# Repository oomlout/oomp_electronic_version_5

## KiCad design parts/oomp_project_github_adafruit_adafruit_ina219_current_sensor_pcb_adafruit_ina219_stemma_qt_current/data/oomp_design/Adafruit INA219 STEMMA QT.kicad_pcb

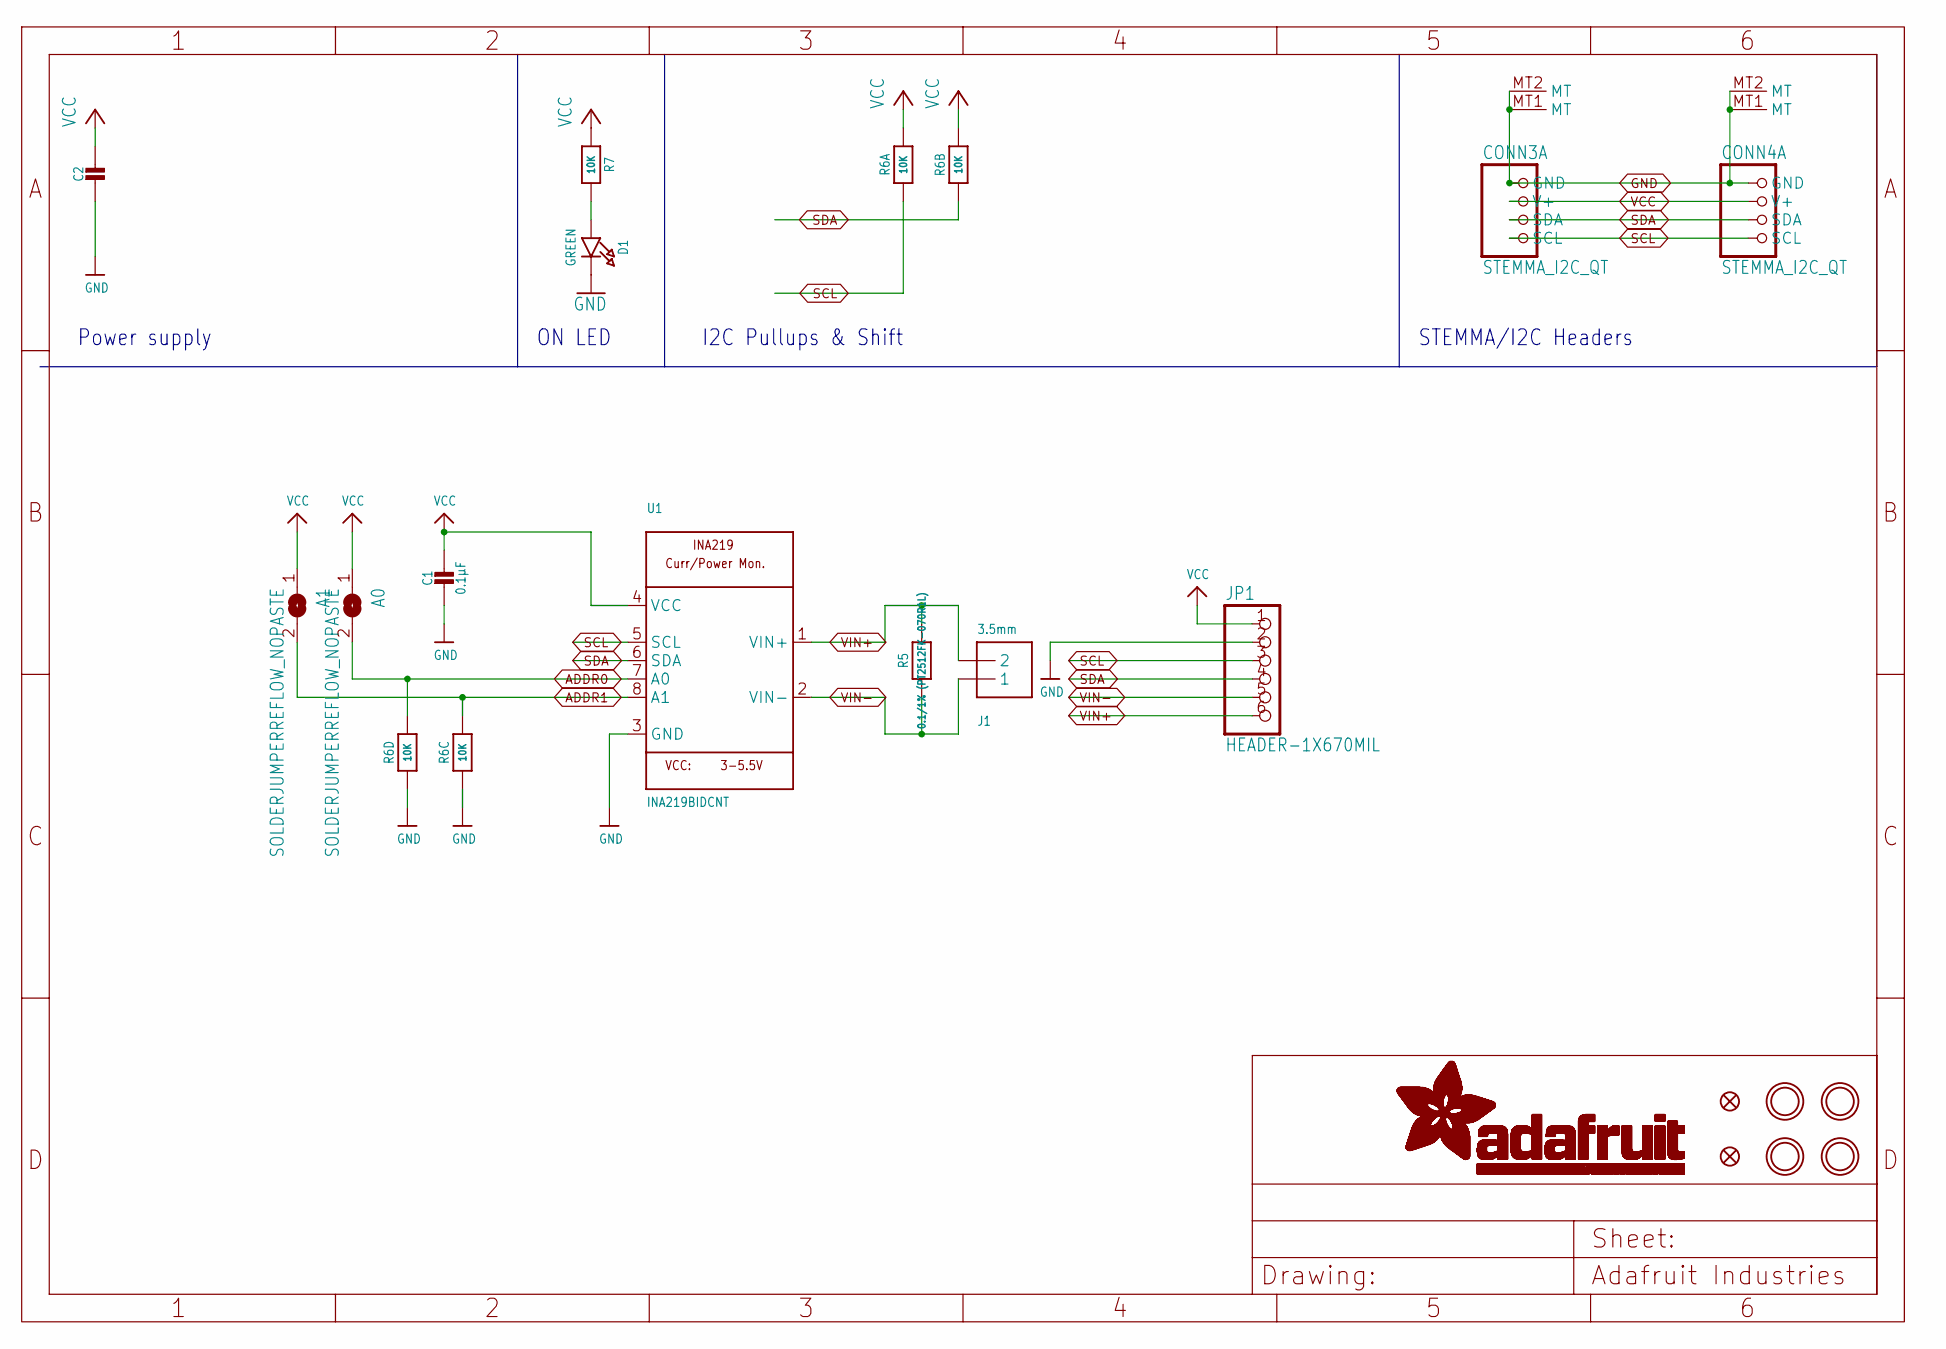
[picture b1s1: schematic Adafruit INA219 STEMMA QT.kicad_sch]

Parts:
A0, A1: SOLDERJUMPERREFLOW_NOPASTE; SOLDERJUMPER_REFLOW_NOPASTE
C1: 0.1µF; 0603-NO
C2: 10uF; 0805-NO
CONN3, CONN4: STEMMA_I2C_QT; JST_SH4
D1: GREEN; CHIPLED_0603_NOOUTLINE
FID3, FID4: FIDUCIAL_1MM
J1: 3.5mm; TERMBLOCK_1X2-3.5MM
JP1: HEADER-1X670MIL; 1X06_ROUND_70
R5: 0.1/1% (PT2512FK-070R1L); 2512
R6: 10K; RESPACK_4X0603
R7: 10K; 0603-NO
U1: INA219BIDCNT; SOT23-8
U$20, U$21, U$25, U$27: MOUNTINGHOLE2.5; MOUNTINGHOLE_2.5_PLATED

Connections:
ADDR0: A0.2, R6.5 (2), U1.7 (A0)
ADDR1: A1.2, R6.6 (2), U1.8 (A1)
GND: C1.2, C2.2, CONN3.1 (GND), CONN3.MT1 (MT), CONN3.MT2 (MT), CONN4.1 (GND), CONN4.MT1 (MT), CONN4.MT2 (MT), D1.C, JP1.2, R6.3 (1), R6.4 (1), U1.3 (GND)
unnamed: D1.A, R7.2
SCL: CONN3.4 (SCL), CONN4.4 (SCL), JP1.3, R6.1, U1.5 (SCL)
SDA: CONN3.3 (SDA), CONN4.3 (SDA), JP1.4, R6.2 (1), U1.6 (SDA)
VCC: A0.1, A1.1, C1.1, C2.1, CONN3.2 (V+), CONN4.2 (V+), JP1.1, R6.7 (2), R6.8 (2), R7.1, U1.4 (VCC)
VIN+: J1.2, JP1.6, R5.2, U1.1 (VIN+)
VIN-: J1.1, JP1.5, R5.1, U1.2 (VIN-)

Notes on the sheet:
ON LED
I2C Pullups & Shift
Power supply
STEMMA/I2C Headers

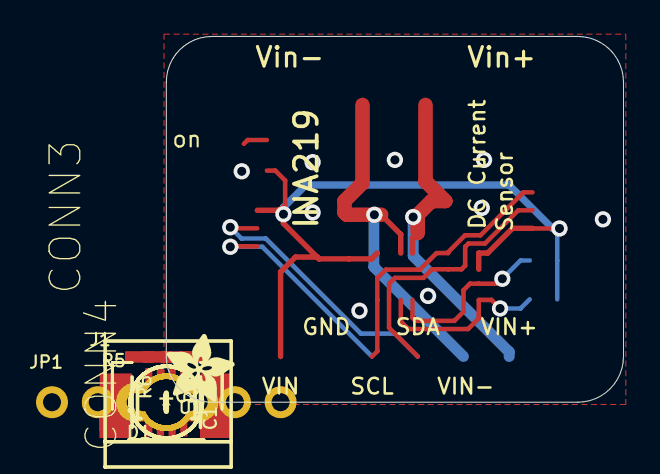
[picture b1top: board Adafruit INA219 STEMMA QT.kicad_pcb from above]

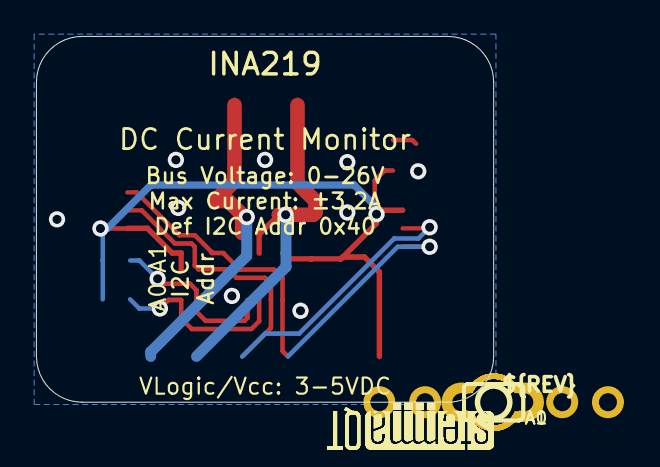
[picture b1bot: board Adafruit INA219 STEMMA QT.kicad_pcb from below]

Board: 2 copper layers, 25.4 x 20.3 mm, 23 parts (5 on the bottom side), 9 nets.

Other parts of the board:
U$29: ADAFRUIT_3.5MM
U$30: PCBFEAT-REV-040
U$31, U$32: STEMMAQT

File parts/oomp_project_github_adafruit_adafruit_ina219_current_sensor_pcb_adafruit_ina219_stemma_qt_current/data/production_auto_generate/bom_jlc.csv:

Comment,Designator,Footprint,LCSC Part #
,JP1,Adafruit INA219 STEMMA QT-import-fps:1X06_ROUND_70,C37208
,U$29,Adafruit INA219 STEMMA QT-import-fps:ADAFRUIT_3.5MM,
,U$30,Adafruit INA219 STEMMA QT-import-fps:PCBFEAT-REV-040,
,"A0,A1",Adafruit INA219 STEMMA QT-import-fps:SOLDERJUMPER_REFLOW_NOPASTE,
,"U$31,U$32",Adafruit INA219 STEMMA QT-import-fps:STEMMAQT,
0.1/1% (PT2512FK-070R1L),R5,Adafruit INA219 STEMMA QT-import-fps:2512,
0.1µF,C1,Adafruit INA219 STEMMA QT-import-fps:0603-NO,C14663
10K,R7,Adafruit INA219 STEMMA QT-import-fps:0603-NO,C98220
10K,R6,Adafruit INA219 STEMMA QT-import-fps:RESPACK_4X0603,C98220
10uF,C2,Adafruit INA219 STEMMA QT-import-fps:0805-NO,
3.5mm,J1,Adafruit INA219 STEMMA QT-import-fps:TERMBLOCK_1X2-3.5MM,
GREEN,D1,Adafruit INA219 STEMMA QT-import-fps:CHIPLED_0603_NOOUTLINE,
INA219BIDCNT,U1,Adafruit INA219 STEMMA QT-import-fps:SOT23-8,
STEMMA_I2C_QT,"CONN3,CONN4",Adafruit INA219 STEMMA QT-import-fps:JST_SH4,C160404

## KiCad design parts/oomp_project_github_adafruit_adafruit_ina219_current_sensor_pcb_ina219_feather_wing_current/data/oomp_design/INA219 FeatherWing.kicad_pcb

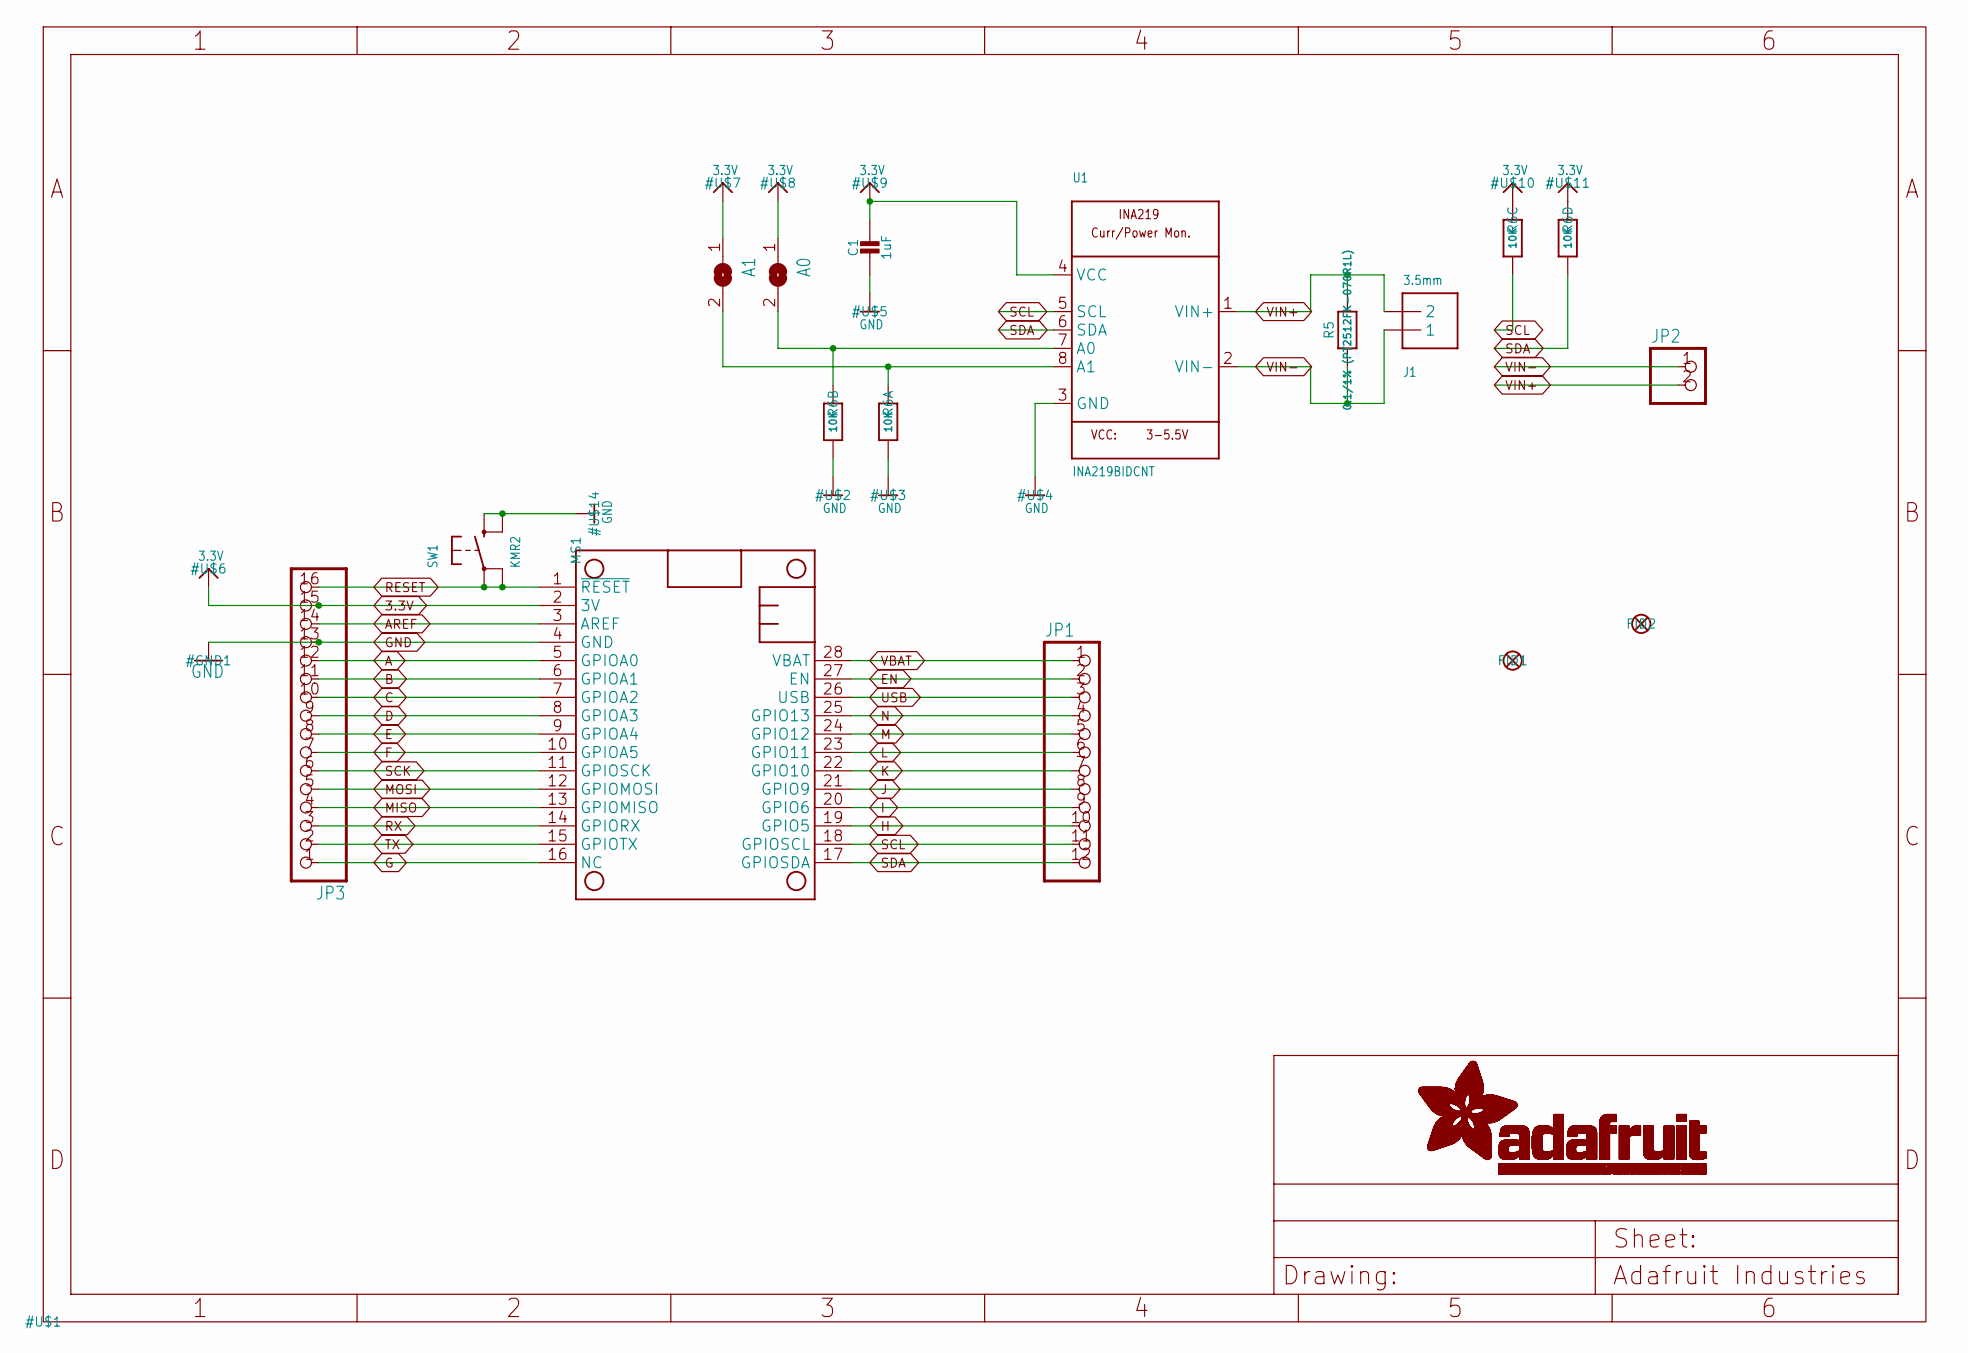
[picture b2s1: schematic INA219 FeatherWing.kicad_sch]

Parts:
A0, A1: SOLDERJUMPERREFLOW_NOPASTE; SOLDERJUMPER_REFLOW_NOPASTE
C1: 1uF; 0805-NO@1
FID1, FID2: FIDUCIAL_1MM
J1: 3.5mm; TERMBLOCK_1X2-3.5MM
JP1: HEADER-1X1276MIL; 1X12_ROUND_76MIL
JP2: HEADER-1X2ROUND; 1X02_ROUND
JP3: HEADER-1X16_76MIL; 1X16_ROUND_76MIL
MS1: FEATHERWING
R5: 0.1/1% (PT2512FK-070R1L); 2512
R6: 10K; RESPACK_4X0603
SW1: KMR2; BTN_KMR2_4.6X2.8
U1: INA219BIDCNT; SOT23-8

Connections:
3.3V: A0.1, A1.1, C1.1, JP3.15, MS1.2 (3V), R6.5 (2), R6.6 (2), U1.4 (VCC)
A: JP3.12, MS1.5 (GPIOA0)
AREF: JP3.14, MS1.3 (AREF)
B: JP3.11, MS1.6 (GPIOA1)
C: JP3.10, MS1.7 (GPIOA2)
D: JP3.9, MS1.8 (GPIOA3)
E: JP3.8, MS1.9 (GPIOA4)
EN: JP1.2, MS1.27 (EN)
F: JP3.7, MS1.10 (GPIOA5)
G: JP3.1, MS1.16 (NC)
GND: C1.2, JP3.13, MS1.4 (GND), R6.7 (2), R6.8 (2), SW1.B (S), SW1.B' (S1), U1.3 (GND)
H: JP1.10, MS1.19 (GPIO5)
I: JP1.9, MS1.20 (GPIO6)
J: JP1.8, MS1.21 (GPIO9)
K: JP1.7, MS1.22 (GPIO10)
L: JP1.6, MS1.23 (GPIO11)
M: JP1.5, MS1.24 (GPIO12)
MISO: JP3.4, MS1.13 (GPIOMISO)
MOSI: JP3.5, MS1.12 (GPIOMOSI)
N: JP1.4, MS1.25 (GPIO13)
unnamed: A1.2, R6.1, U1.8 (A1)
unnamed: A0.2, R6.2 (1), U1.7 (A0)
RESET: JP3.16, MS1.1 (~RESET), SW1.A, SW1.A' (P1)
RX: JP3.3, MS1.14 (GPIORX)
SCK: JP3.6, MS1.11 (GPIOSCK)
SCL: JP1.11, MS1.18 (GPIOSCL), R6.3 (1), U1.5 (SCL)
SDA: JP1.12, MS1.17 (GPIOSDA), R6.4 (1), U1.6 (SDA)
TX: JP3.2, MS1.15 (GPIOTX)
USB: JP1.3, MS1.26 (USB)
VBAT: JP1.1, MS1.28 (VBAT)
VIN+: J1.2, JP2.2, R5.2, U1.1 (VIN+)
VIN-: J1.1, JP2.1, R5.1, U1.2 (VIN-)

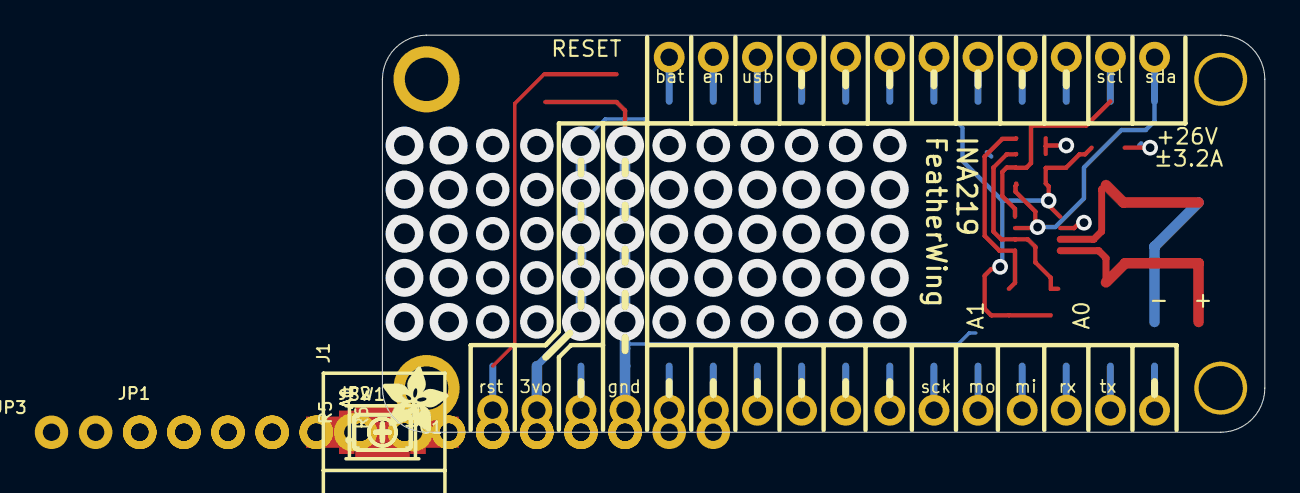
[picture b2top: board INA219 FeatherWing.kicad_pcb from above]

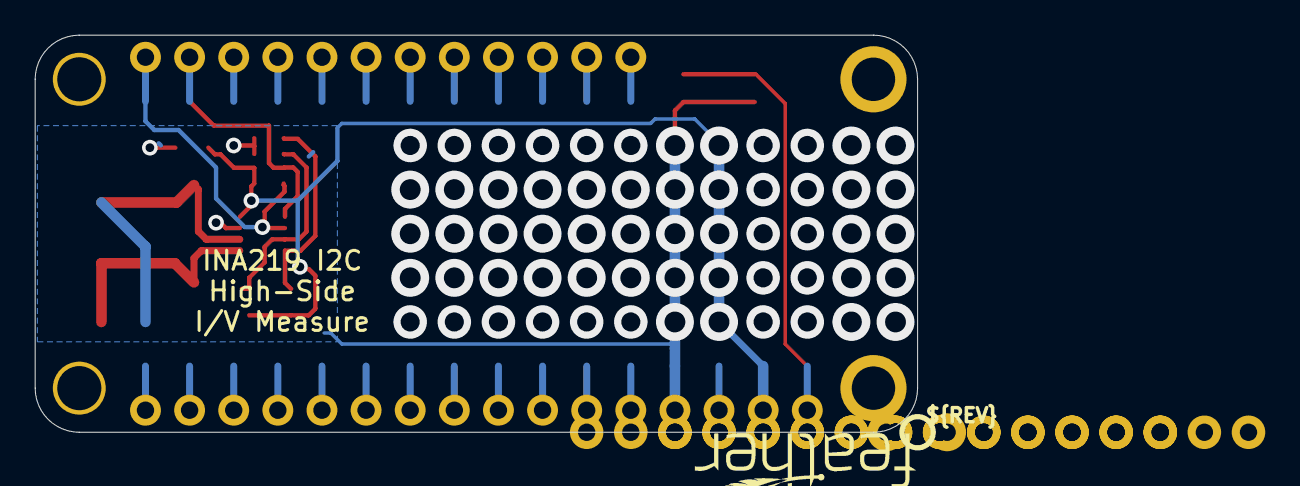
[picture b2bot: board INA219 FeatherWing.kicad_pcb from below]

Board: 2 copper layers, 50.8 x 22.9 mm, 19 parts (2 on the bottom side), 32 nets.

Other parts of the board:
U$12: SYMBOL_PLUS
U$13: SYMBOL_MINUS
U$15: FEATHERLOGO_SMALL
U$16: ADAFRUIT_3.5MM
U$17: PCBFEAT-REV-040

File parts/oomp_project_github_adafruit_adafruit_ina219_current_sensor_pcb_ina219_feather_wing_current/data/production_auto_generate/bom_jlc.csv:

Comment,Designator,Footprint,LCSC Part #
,JP2,INA219 FeatherWing-import-fps:1X02_ROUND,C492401
,JP1,INA219 FeatherWing-import-fps:1X12_ROUND_76MIL,C7501588
,JP3,INA219 FeatherWing-import-fps:1X16_ROUND_76MIL,C7501270
,U$16,INA219 FeatherWing-import-fps:ADAFRUIT_3.5MM,
,U$15,INA219 FeatherWing-import-fps:FEATHERLOGO_SMALL,
,U$17,INA219 FeatherWing-import-fps:PCBFEAT-REV-040,
,"A0,A1",INA219 FeatherWing-import-fps:SOLDERJUMPER_REFLOW_NOPASTE,
,U$13,INA219 FeatherWing-import-fps:SYMBOL_MINUS,
,U$12,INA219 FeatherWing-import-fps:SYMBOL_PLUS,
0.1/1% (PT2512FK-070R1L),R5,INA219 FeatherWing-import-fps:2512,
10K,R6,INA219 FeatherWing-import-fps:RESPACK_4X0603,C98220
1uF,C1,INA219 FeatherWing-import-fps:0805-NO@1,
3.5mm,J1,INA219 FeatherWing-import-fps:TERMBLOCK_1X2-3.5MM,
FEATHERWING,MS1,INA219 FeatherWing-import-fps:FEATHERWING,
INA219BIDCNT,U1,INA219 FeatherWing-import-fps:SOT23-8,
KMR2,SW1,INA219 FeatherWing-import-fps:BTN_KMR2_4.6X2.8,

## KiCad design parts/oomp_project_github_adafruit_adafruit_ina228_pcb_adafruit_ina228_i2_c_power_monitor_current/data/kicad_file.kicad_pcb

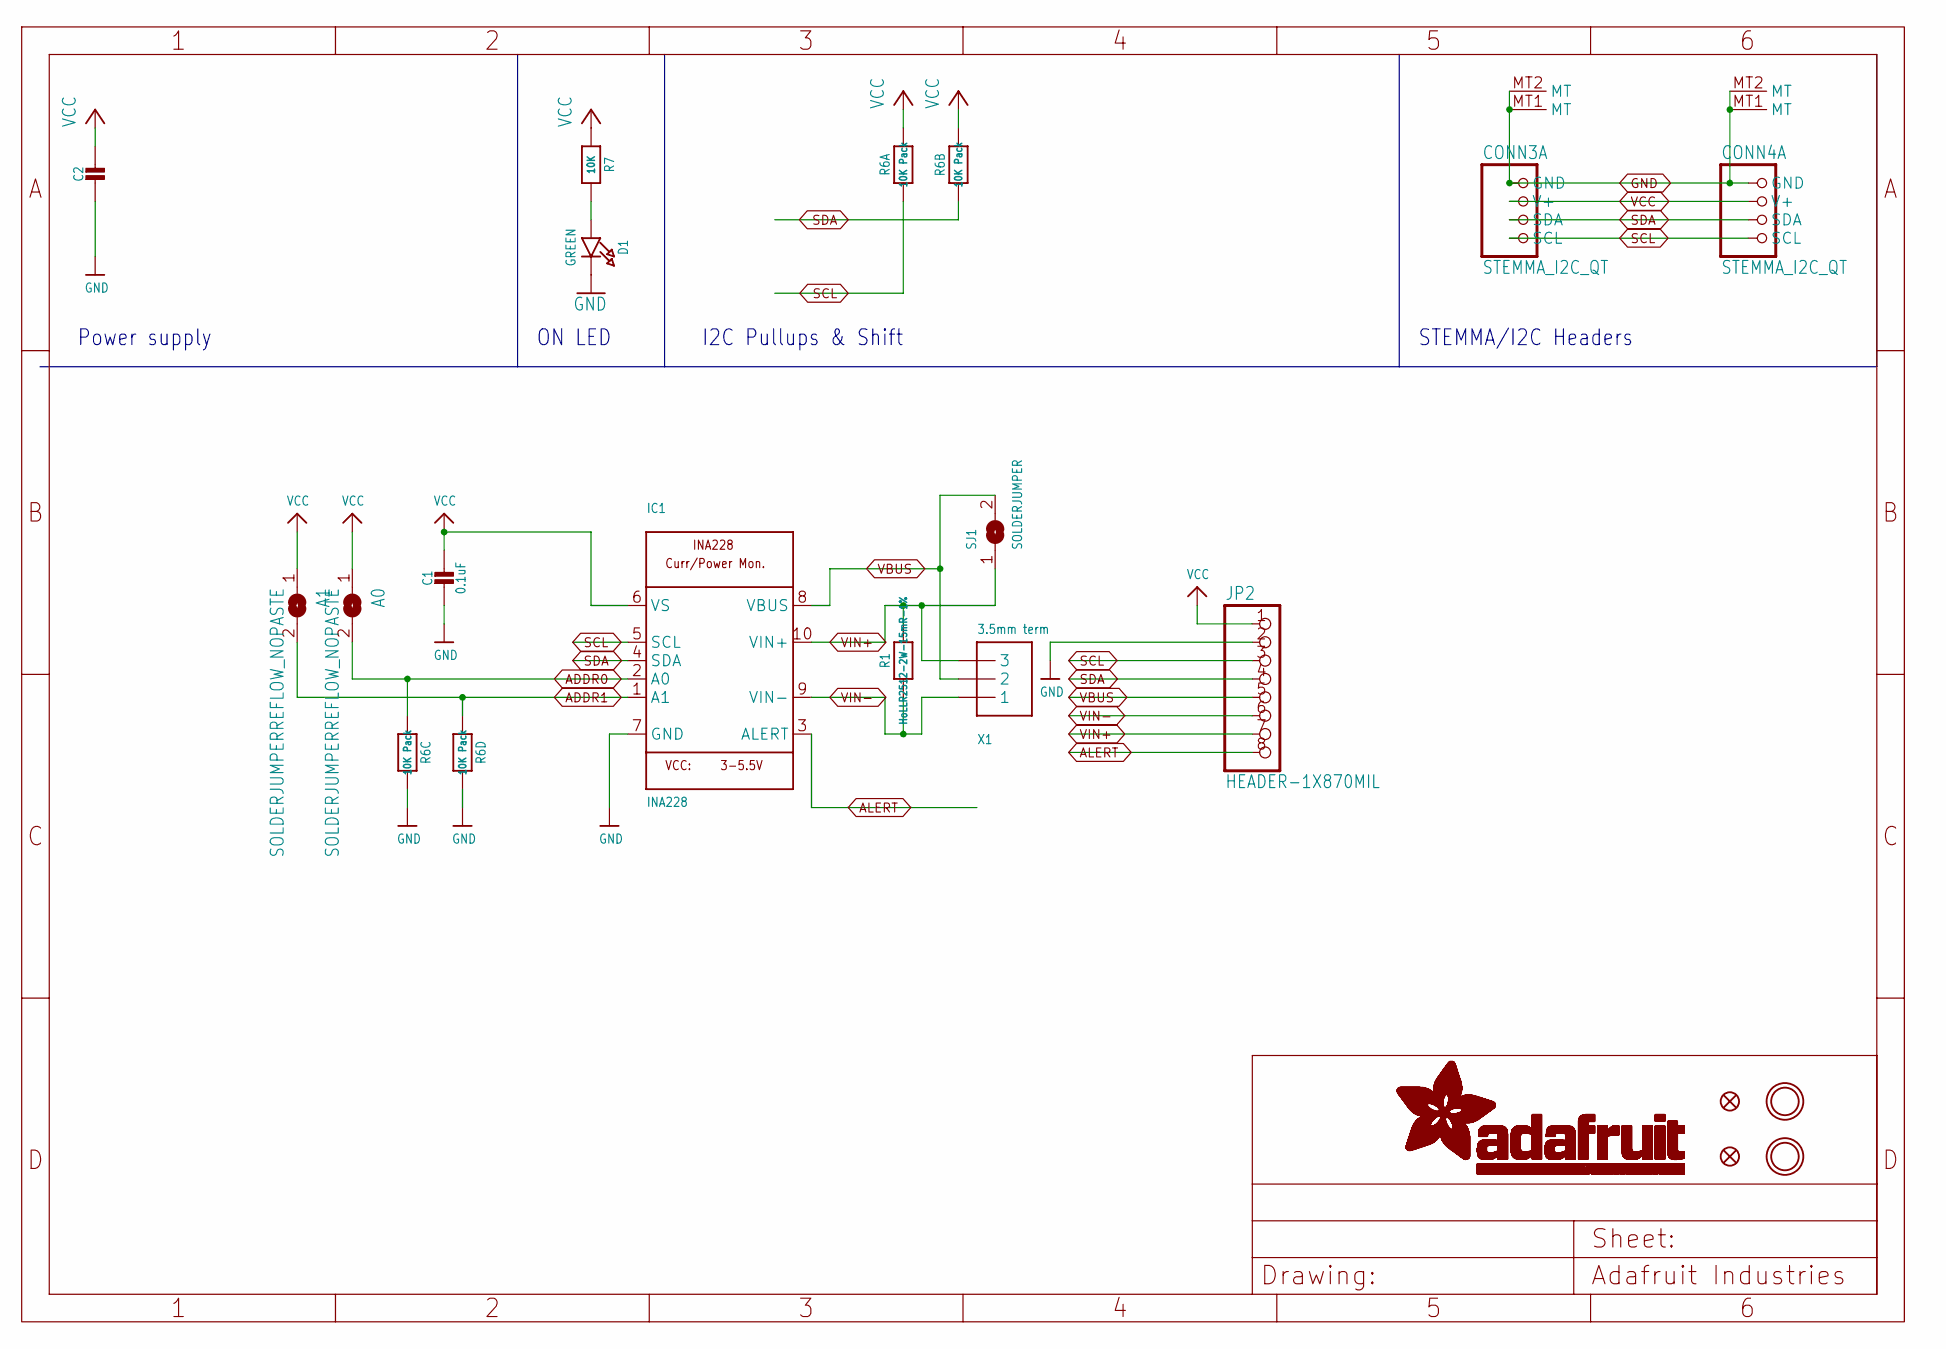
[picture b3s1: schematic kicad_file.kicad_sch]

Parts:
A0, A1: SOLDERJUMPERREFLOW_NOPASTE; SOLDERJUMPER_REFLOW_NOPASTE
C1: 0.1uF; 0603-NO
C2: 10uF; 0805-NO
CONN3, CONN4: STEMMA_I2C_QT; JST_SH4; LCSC C2845363
D1: GREEN; CHIPLED_0603_NOOUTLINE
FID3, FID4: FIDUCIAL_1MM
IC1: INA228; MSOP10
JP2: HEADER-1X870MIL; 1X08_ROUND_70
R1: HoLLR2512-2W-15mR-1%; 2512
R6: 10K Pack; RESPACK_4X0603
R7: 10K; 0603-NO
SJ1: SOLDERJUMPER; SOLDERJUMPER_ARROW_NOPASTE
U$20, U$21: MOUNTINGHOLE2.5; MOUNTINGHOLE_2.5_PLATED
X1: 3.5mm term; TERMBLOCK_1X3-3.5MM

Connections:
ADDR0: A0.2, IC1.2 (A0), R6.3 (1)
ADDR1: A1.2, IC1.1 (A1), R6.4 (1)
ALERT: IC1.3 (ALERT), JP2.8
GND: C1.2, C2.2, CONN3.1 (GND), CONN3.MT1 (MT), CONN3.MT2 (MT), CONN4.1 (GND), CONN4.MT1 (MT), CONN4.MT2 (MT), D1.C, IC1.7 (GND), JP2.2, R6.5 (2), R6.6 (2)
unnamed: D1.A, R7.2
SCL: CONN3.4 (SCL), CONN4.4 (SCL), IC1.5 (SCL), JP2.3, R6.1
SDA: CONN3.3 (SDA), CONN4.3 (SDA), IC1.4 (SDA), JP2.4, R6.2 (1)
VBUS: IC1.8 (VBUS), JP2.5, SJ1.2, X1.2
VCC: A0.1, A1.1, C1.1, C2.1, CONN3.2 (V+), CONN4.2 (V+), IC1.6 (VS), JP2.1, R6.7 (2), R6.8 (2), R7.1
VIN+: IC1.10 (VIN+), JP2.7, R1.2, SJ1.1, X1.3
VIN-: IC1.9 (VIN-), JP2.6, R1.1, X1.1

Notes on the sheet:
ON LED
Power supply
I2C Pullups & Shift
STEMMA/I2C Headers

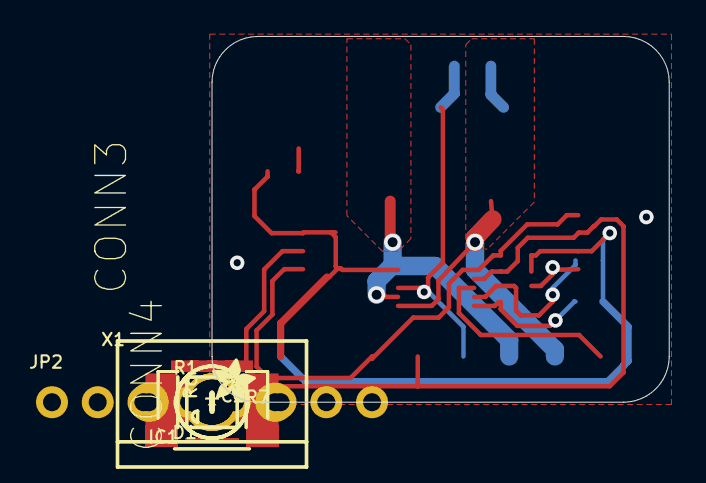
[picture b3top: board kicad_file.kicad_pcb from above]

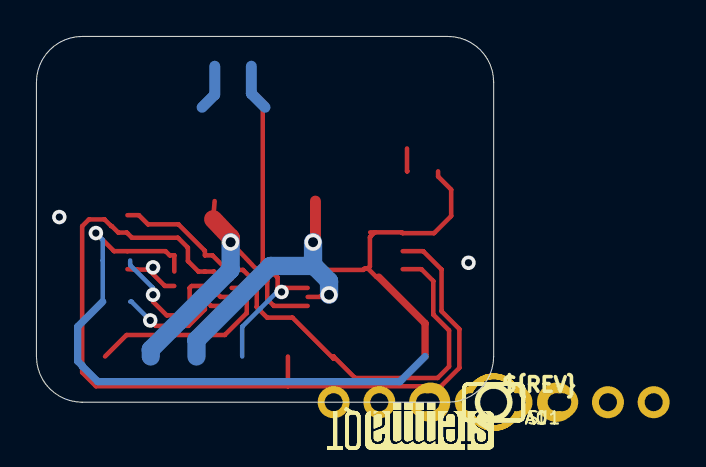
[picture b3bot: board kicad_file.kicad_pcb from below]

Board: 2 copper layers, 25.4 x 20.3 mm, 43 parts (16 on the bottom side), 11 nets.

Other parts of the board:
PLABEL0: PLABEL0
PLABEL1: PLABEL1
PLABEL2: PLABEL2
PLABEL3: PLABEL3
PLABEL4: PLABEL4
PLABEL5: PLABEL5
PLABEL6: PLABEL6
PLABEL7: PLABEL7
PLABEL8: PLABEL8
PLABEL9: PLABEL9
PLABEL10: PLABEL10
PLABEL11: PLABEL11
PLABEL12: PLABEL12
PLABEL13: PLABEL13
PLABEL14: PLABEL14
PLABEL15: PLABEL15
PLABEL16: PLABEL16
PLABEL17: PLABEL17
PLABEL18: PLABEL18
PLABEL19: PLABEL19
PLABEL20: PLABEL20
U$1: ADAFRUIT_2.5MM
U$30: PCBFEAT-REV-040
U$31, U$32: STEMMAQT

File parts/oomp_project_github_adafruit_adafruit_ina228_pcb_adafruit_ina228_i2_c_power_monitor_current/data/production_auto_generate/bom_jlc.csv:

Comment,Designator,Footprint,LCSC Part #
,JP2,Adafruit INA228 I2C Power Monitor-import-fps:1X08_ROUND_70,C492421
,U$1,Adafruit INA228 I2C Power Monitor-import-fps:ADAFRUIT_2.5MM,
,U$30,Adafruit INA228 I2C Power Monitor-import-fps:PCBFEAT-REV-040,
,PLABEL0,Adafruit INA228 I2C Power Monitor-import-fps:PLABEL0,
,PLABEL1,Adafruit INA228 I2C Power Monitor-import-fps:PLABEL1,
,PLABEL10,Adafruit INA228 I2C Power Monitor-import-fps:PLABEL10,
,PLABEL11,Adafruit INA228 I2C Power Monitor-import-fps:PLABEL11,
,PLABEL12,Adafruit INA228 I2C Power Monitor-import-fps:PLABEL12,
,PLABEL13,Adafruit INA228 I2C Power Monitor-import-fps:PLABEL13,
,PLABEL14,Adafruit INA228 I2C Power Monitor-import-fps:PLABEL14,
,PLABEL15,Adafruit INA228 I2C Power Monitor-import-fps:PLABEL15,
,PLABEL16,Adafruit INA228 I2C Power Monitor-import-fps:PLABEL16,
,PLABEL17,Adafruit INA228 I2C Power Monitor-import-fps:PLABEL17,
,PLABEL18,Adafruit INA228 I2C Power Monitor-import-fps:PLABEL18,
,PLABEL19,Adafruit INA228 I2C Power Monitor-import-fps:PLABEL19,
,PLABEL2,Adafruit INA228 I2C Power Monitor-import-fps:PLABEL2,
,PLABEL20,Adafruit INA228 I2C Power Monitor-import-fps:PLABEL20,
,PLABEL3,Adafruit INA228 I2C Power Monitor-import-fps:PLABEL3,
,PLABEL4,Adafruit INA228 I2C Power Monitor-import-fps:PLABEL4,
,PLABEL5,Adafruit INA228 I2C Power Monitor-import-fps:PLABEL5,
,PLABEL6,Adafruit INA228 I2C Power Monitor-import-fps:PLABEL6,
,PLABEL7,Adafruit INA228 I2C Power Monitor-import-fps:PLABEL7,
,PLABEL8,Adafruit INA228 I2C Power Monitor-import-fps:PLABEL8,
,PLABEL9,Adafruit INA228 I2C Power Monitor-import-fps:PLABEL9,
,"A0,A1",Adafruit INA228 I2C Power Monitor-import-fps:SOLDERJUMPER_REFLOW_NOPASTE,
,"U$31,U$32",Adafruit INA228 I2C Power Monitor-import-fps:STEMMAQT,
0.1uF,C1,Adafruit INA228 I2C Power Monitor-import-fps:0603-NO,C14663
10K,R7,Adafruit INA228 I2C Power Monitor-import-fps:0603-NO,C98220
10K Pack,R6,Adafruit INA228 I2C Power Monitor-import-fps:RESPACK_4X0603,C98220
10uF,C2,Adafruit INA228 I2C Power Monitor-import-fps:0805-NO,
3.5mm term,X1,Adafruit INA228 I2C Power Monitor-import-fps:TERMBLOCK_1X3-3.5MM,
GREEN,D1,Adafruit INA228 I2C Power Monitor-import-fps:CHIPLED_0603_NOOUTLINE,
HoLLR2512-2W-15mR-1%,R1,Adafruit INA228 I2C Power Monitor-import-fps:2512,
INA228,IC1,Adafruit INA228 I2C Power Monitor-import-fps:MSOP10,
STEMMA_I2C_QT,"CONN3,CONN4",Adafruit INA228 I2C Power Monitor-import-fps:JST_SH4,C160404

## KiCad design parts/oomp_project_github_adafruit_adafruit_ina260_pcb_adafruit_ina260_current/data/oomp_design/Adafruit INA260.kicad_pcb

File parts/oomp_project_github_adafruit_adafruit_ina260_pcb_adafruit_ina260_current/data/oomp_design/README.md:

# OOMP KiCad design copy

Open `Adafruit INA260.kicad_pro` (or the `.kicad_pcb` / `.kicad_sch`) in KiCad. Local OOMP libraries are under `libraries/`. Original inputs are preserved in [../original/](../original/).

Only verified unchanged installed KiCad defaults were renamed. Modified, custom, unmatched and unavailable items remain unchanged. Soldering variants are never swapped during conversion. Existing pad coordinates, nets and UUIDs are preserved.

See [conversion_report.yaml](conversion_report.yaml) for every conversion and skip. Copy this directory before editing; regeneration refuses to overwrite edited design files.

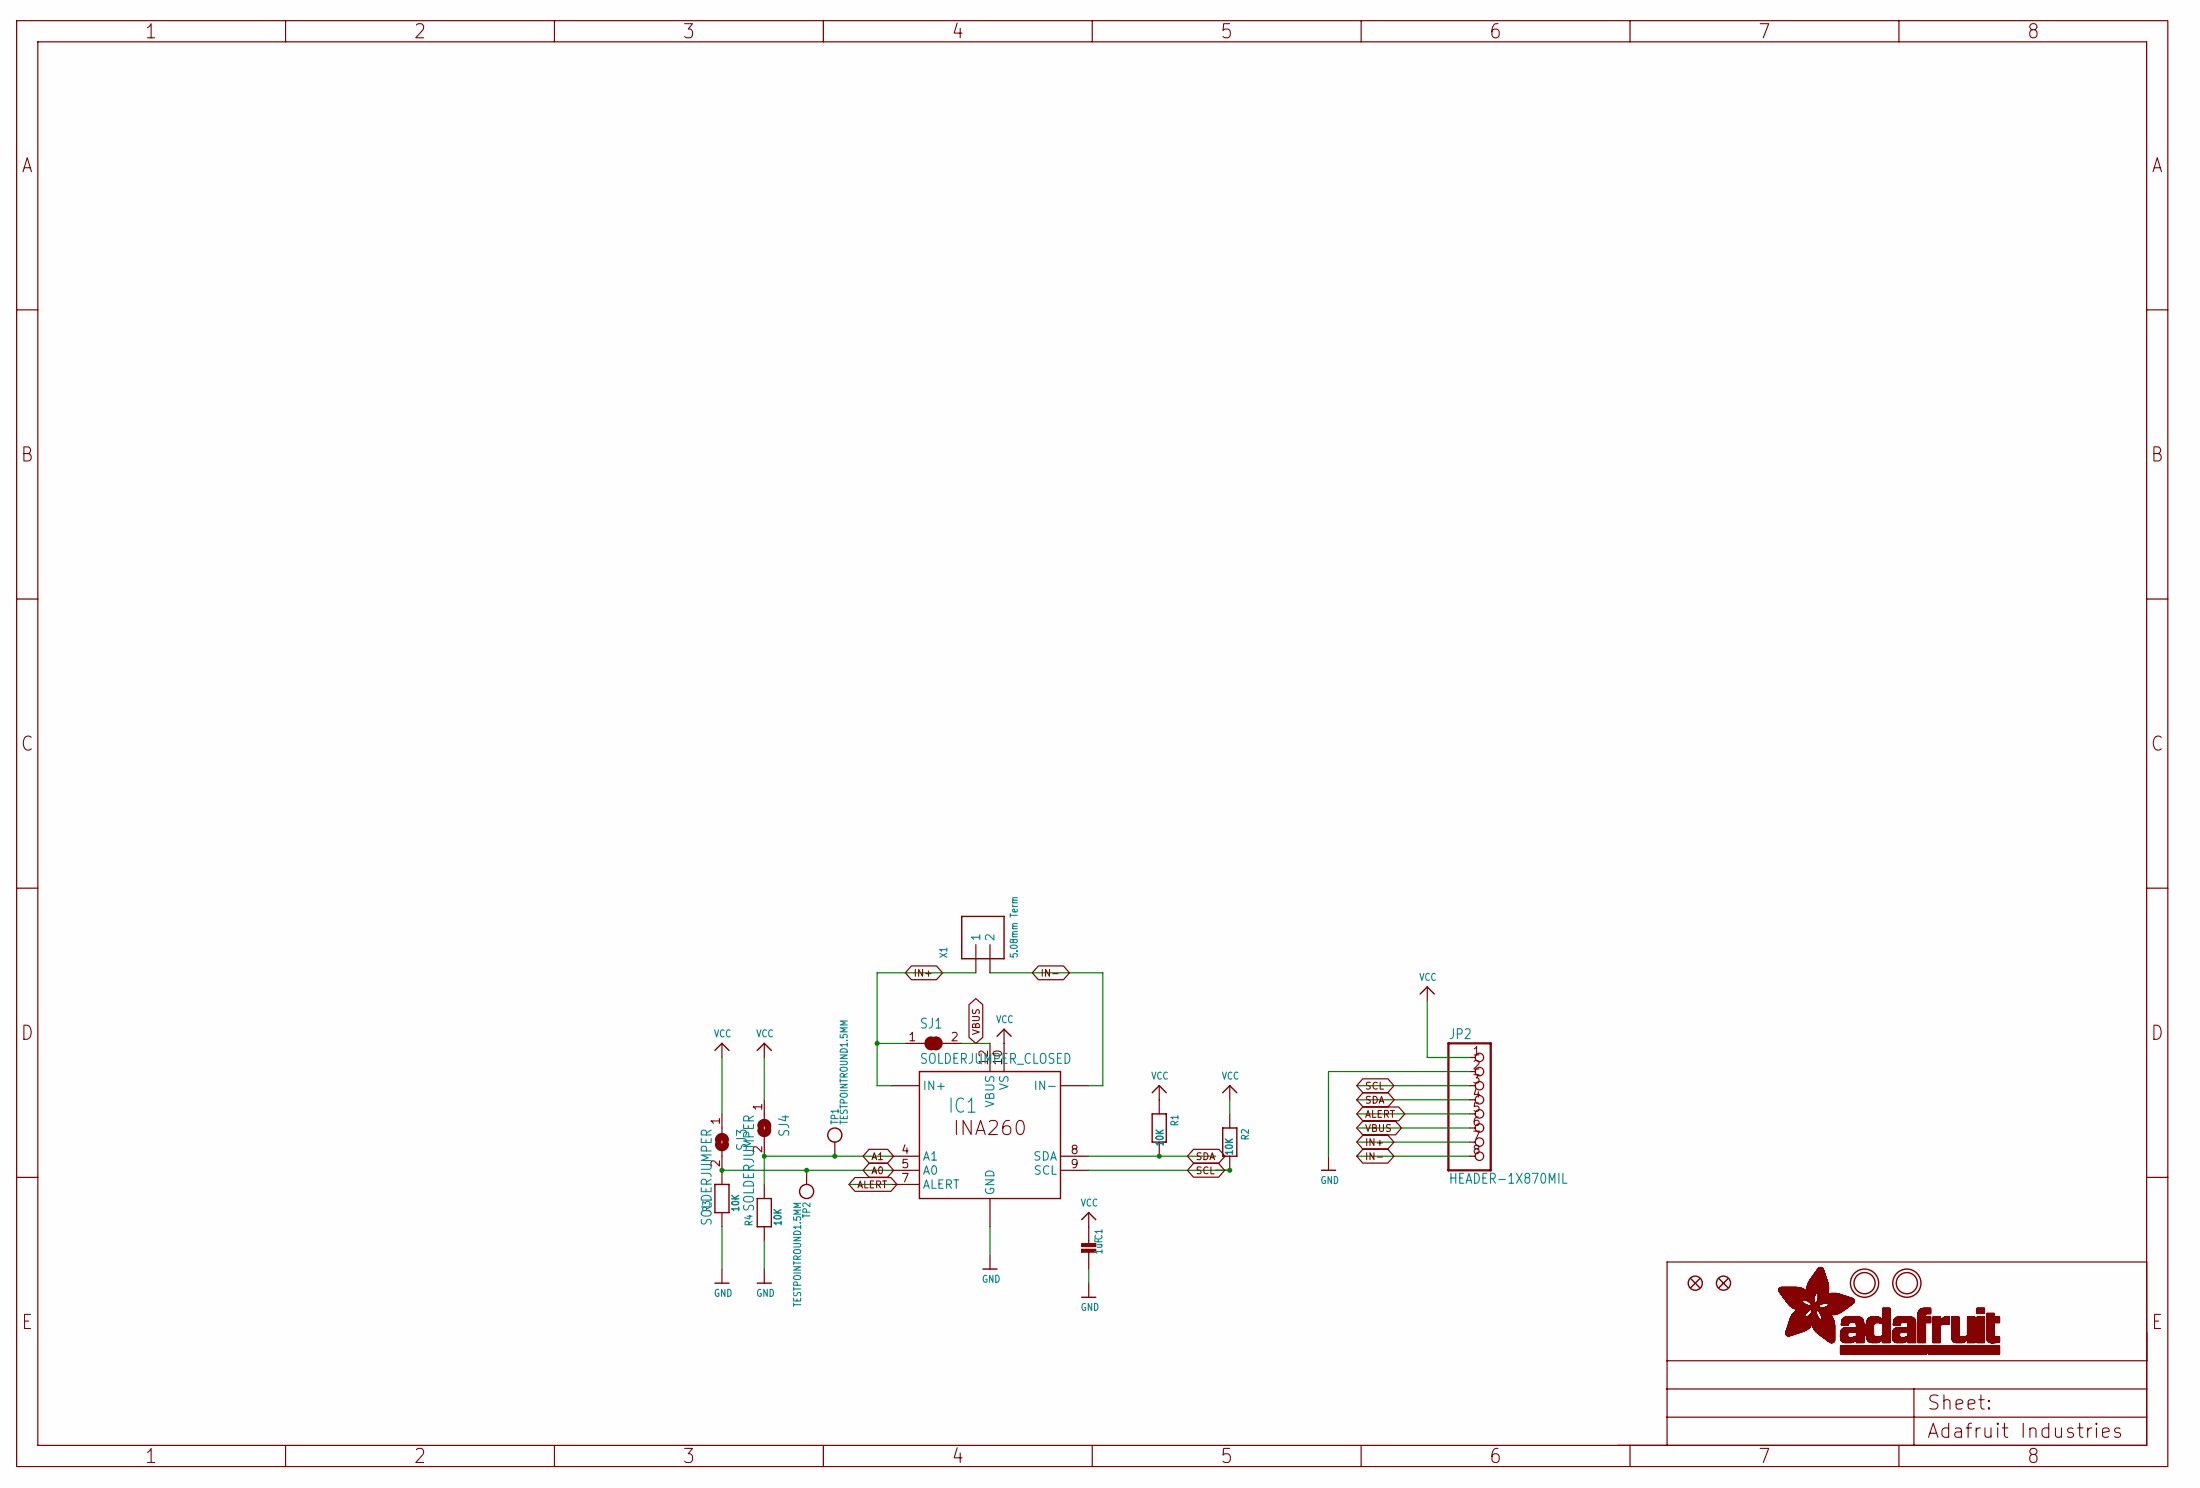
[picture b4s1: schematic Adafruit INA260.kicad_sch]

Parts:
C1: 1uF; 0603-NO
FID3, FID4: MICROBUILDER_FIDUCIAL""; MICROBUILDER_FIDUCIAL_1MM
IC1: INA260; TSSOP16
JP2: HEADER-1X870MIL; 1X08_ROUND_70
R1, R2, R3, R4: 10K; 0603-NO
SJ1: SOLDERJUMPER_CLOSED; SOLDERJUMPER_CLOSEDWIRE
SJ3, SJ4: SOLDERJUMPER; SOLDERJUMPER_ARROW_NOPASTE
TP1, TP2: TESTPOINTROUND1.5MM; TESTPOINT_ROUND_1.5MM
U$7, U$8: MOUNTINGHOLE2.5; MOUNTINGHOLE_2.5_PLATED
X1: 5.08mm Term; TERMBLOCK_508_1X2

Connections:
A0: IC1.5 (A0), R3.2, SJ3.2, TP2.P$1
A1: IC1.4 (A1), R4.2, SJ4.2, TP1.P$1
ALERT: IC1.7 (ALERT), JP2.5
GND: C1.2, IC1.6 (GND), IC1.11 (GND), IC1.13 (GND), JP2.2, R3.1, R4.1
IN+: IC1.1 (IN+), IC1.2 (IN+), IC1.3 (IN+), JP2.7, SJ1.1, X1.P$3 (1)
IN-: IC1.14 (IN-), IC1.15 (IN-), IC1.16 (IN-), JP2.8, X1.P$4 (2)
SCL: IC1.9 (SCL), JP2.3, R2.2
SDA: IC1.8 (SDA), JP2.4, R1.2
VBUS: IC1.12 (VBUS), JP2.6, SJ1.2
VCC: C1.1, IC1.10 (VS), JP2.1, R1.1, R2.1, SJ3.1, SJ4.1

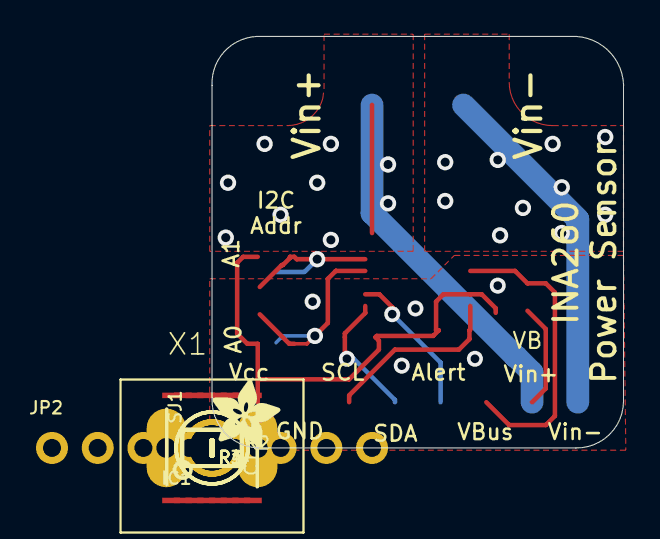
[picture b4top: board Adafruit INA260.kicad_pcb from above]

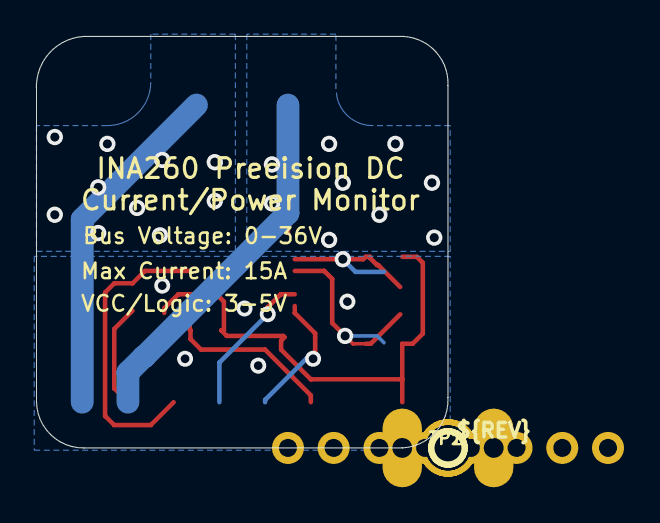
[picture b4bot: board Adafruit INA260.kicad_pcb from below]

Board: 2 copper layers, 22.9 x 22.9 mm, 19 parts (3 on the bottom side), 10 nets.

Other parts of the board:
U$1: ADAFRUIT_3.5MM
U$6: PCBFEAT-REV-040
